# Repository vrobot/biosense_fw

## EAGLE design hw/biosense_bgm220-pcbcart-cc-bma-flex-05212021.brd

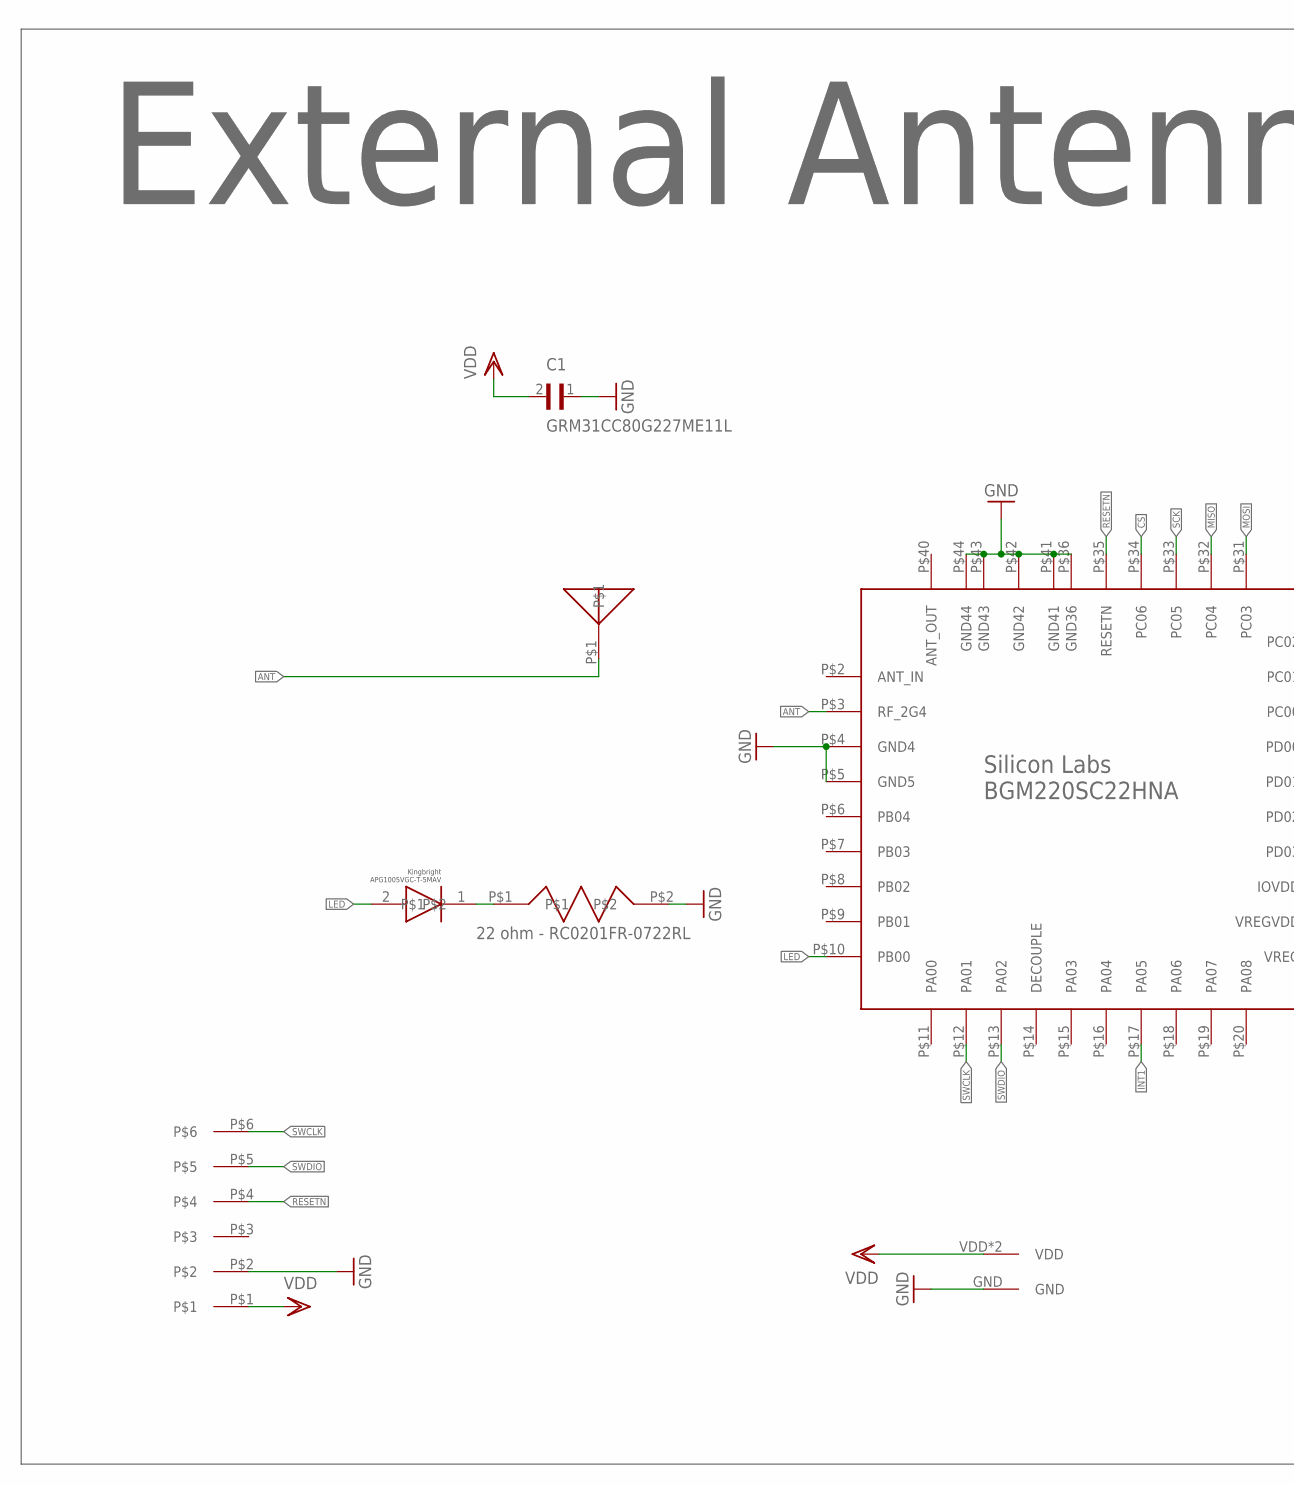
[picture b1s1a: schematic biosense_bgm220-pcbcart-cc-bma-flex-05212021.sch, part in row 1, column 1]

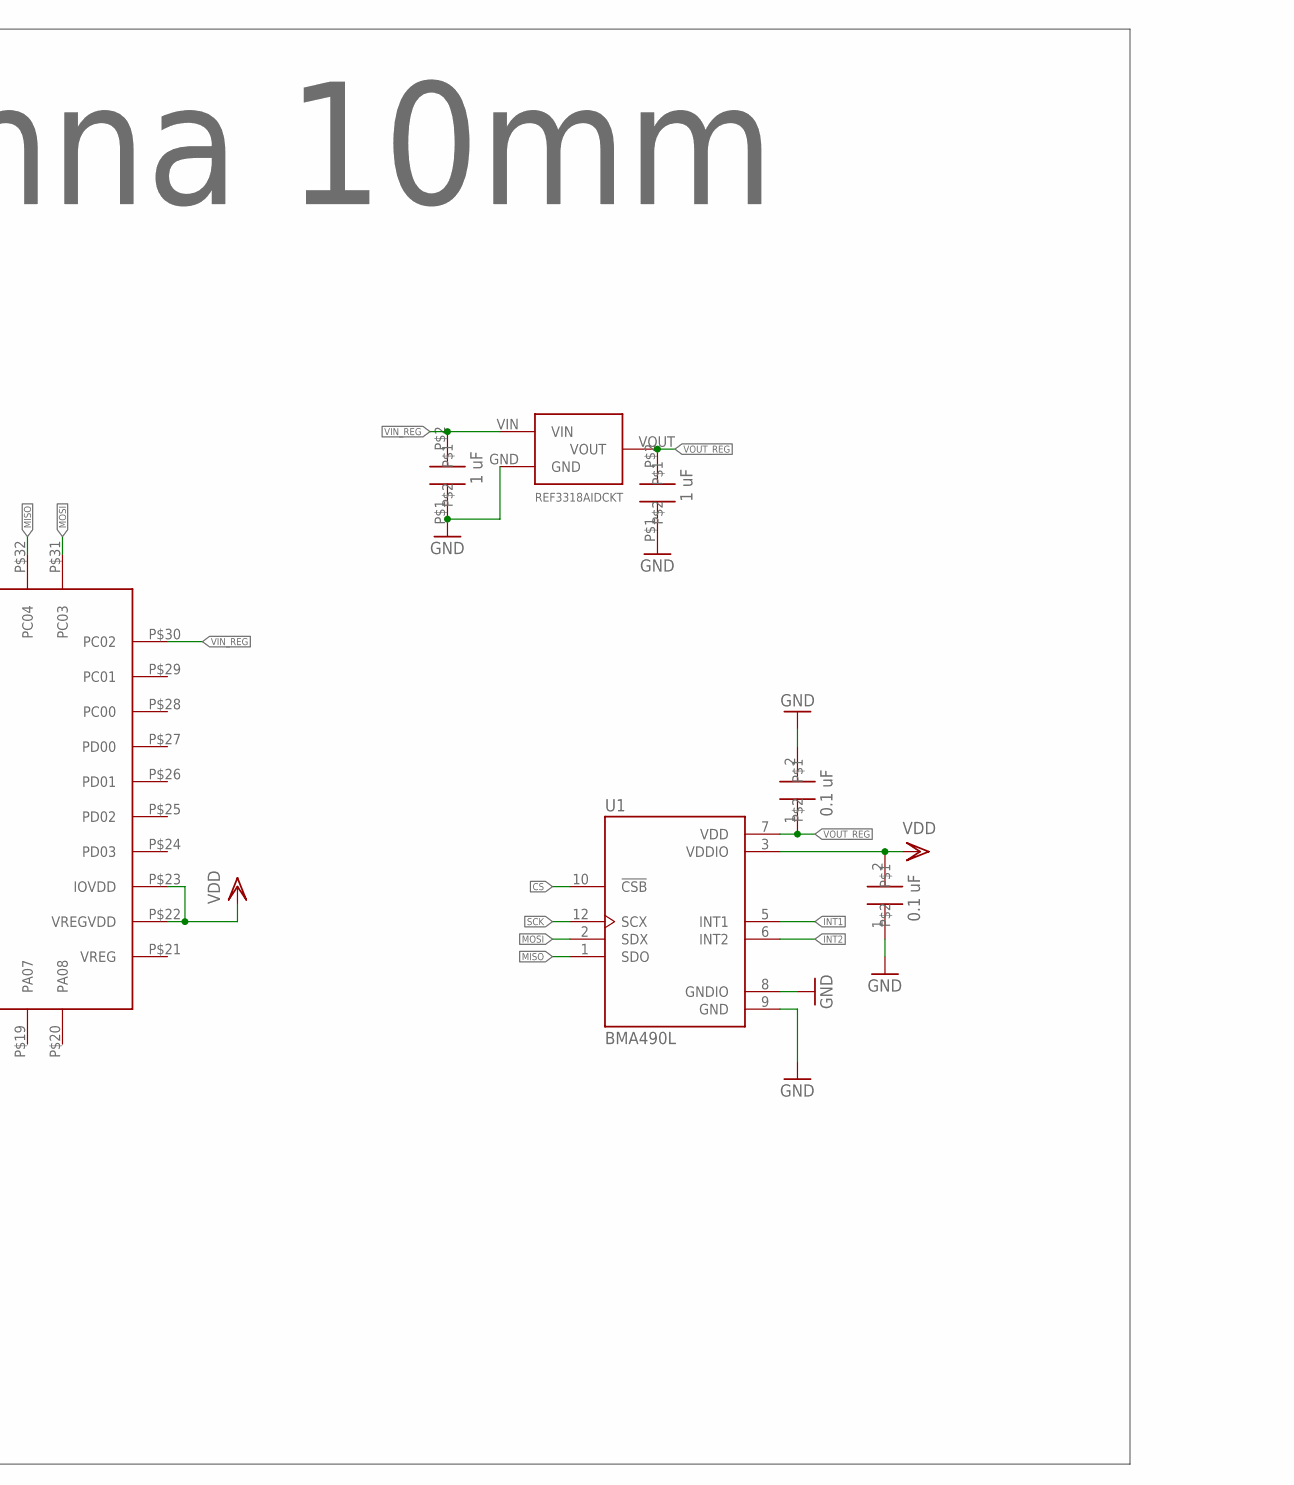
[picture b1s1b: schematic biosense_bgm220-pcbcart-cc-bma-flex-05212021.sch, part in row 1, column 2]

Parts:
C1: GRM31CC80G227ME11L; CAP3216X125N
R1: LEDRC0402N-L; RC0402N-L
U1: BMA490L
U$1: BGM220SC22HNA
U$2, U$3: 0U1_CAPACITOR; FOOTPRINT_01005
U$4: FPCHEADER
U$5: 2450AT18A100
U$6: REF3318; SOT-SC70
U$7: CR1025HOLDERCR1025_3; CR1025_3
U$9, U$10: 1U_CAPACITOR; FOOTPRINT_0201
U$25: 22OHMRESISTOR; FOOTPRINT_0201

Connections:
ANT: U$1.P$3 (RF_2G4), U$5.P$1
CS: U1.10 (!CSB), U$1.P$34 (PC06)
GND: C1.1, U1.8 (GNDIO), U1.9 (GND), U$1.P$4 (GND4), U$1.P$5 (GND5), U$1.P$36 (GND36), U$1.P$41 (GND41), U$1.P$42 (GND42), U$1.P$43 (GND43), U$1.P$44 (GND44), U$2.1, U$3.2, U$4.P$2, U$6.GND, U$7.GND, U$9.P$1, U$10.P$1, U$25.P$2
INT1: U1.5 (INT1), U$1.P$17 (PA05)
INT2: U1.6 (INT2)
LED: R1.2, U$1.P$10 (PB00)
MISO: U1.1 (SDO), U$1.P$32 (PC04)
MOSI: U1.2 (SDX), U$1.P$31 (PC03)
unnamed: R1.1, U$25.P$1
RESETN: U$1.P$35 (RESETN), U$4.P$4
SCK: U1.12 (SCX), U$1.P$33 (PC05)
SWCLK: U$1.P$12 (PA01), U$4.P$6
SWDIO: U$1.P$13 (PA02), U$4.P$5
VDD: C1.2, U1.3 (VDDIO), U$1.P$22 (VREGVDD), U$1.P$23 (IOVDD), U$2.2, U$4.P$1, U$7.VDD, U$7.VDD2 (VDD)
VIN_REG: U$1.P$30 (PC02), U$6.VIN, U$9.P$2
VOUT_REG: U1.7 (VDD), U$3.1, U$6.VOUT, U$10.P$2

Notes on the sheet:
External Antenna 10mm

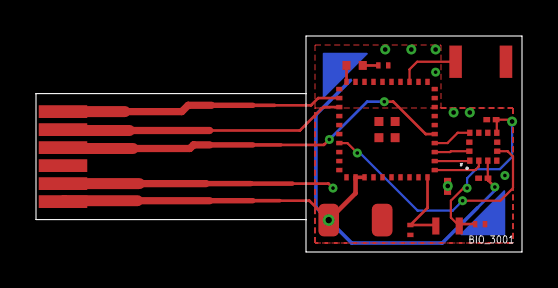
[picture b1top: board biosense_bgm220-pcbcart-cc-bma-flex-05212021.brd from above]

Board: 2 copper layers, 27.0 x 12.0 mm, 13 parts (1 on the bottom side), 15 nets.

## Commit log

2022-06-14 biosense fw
